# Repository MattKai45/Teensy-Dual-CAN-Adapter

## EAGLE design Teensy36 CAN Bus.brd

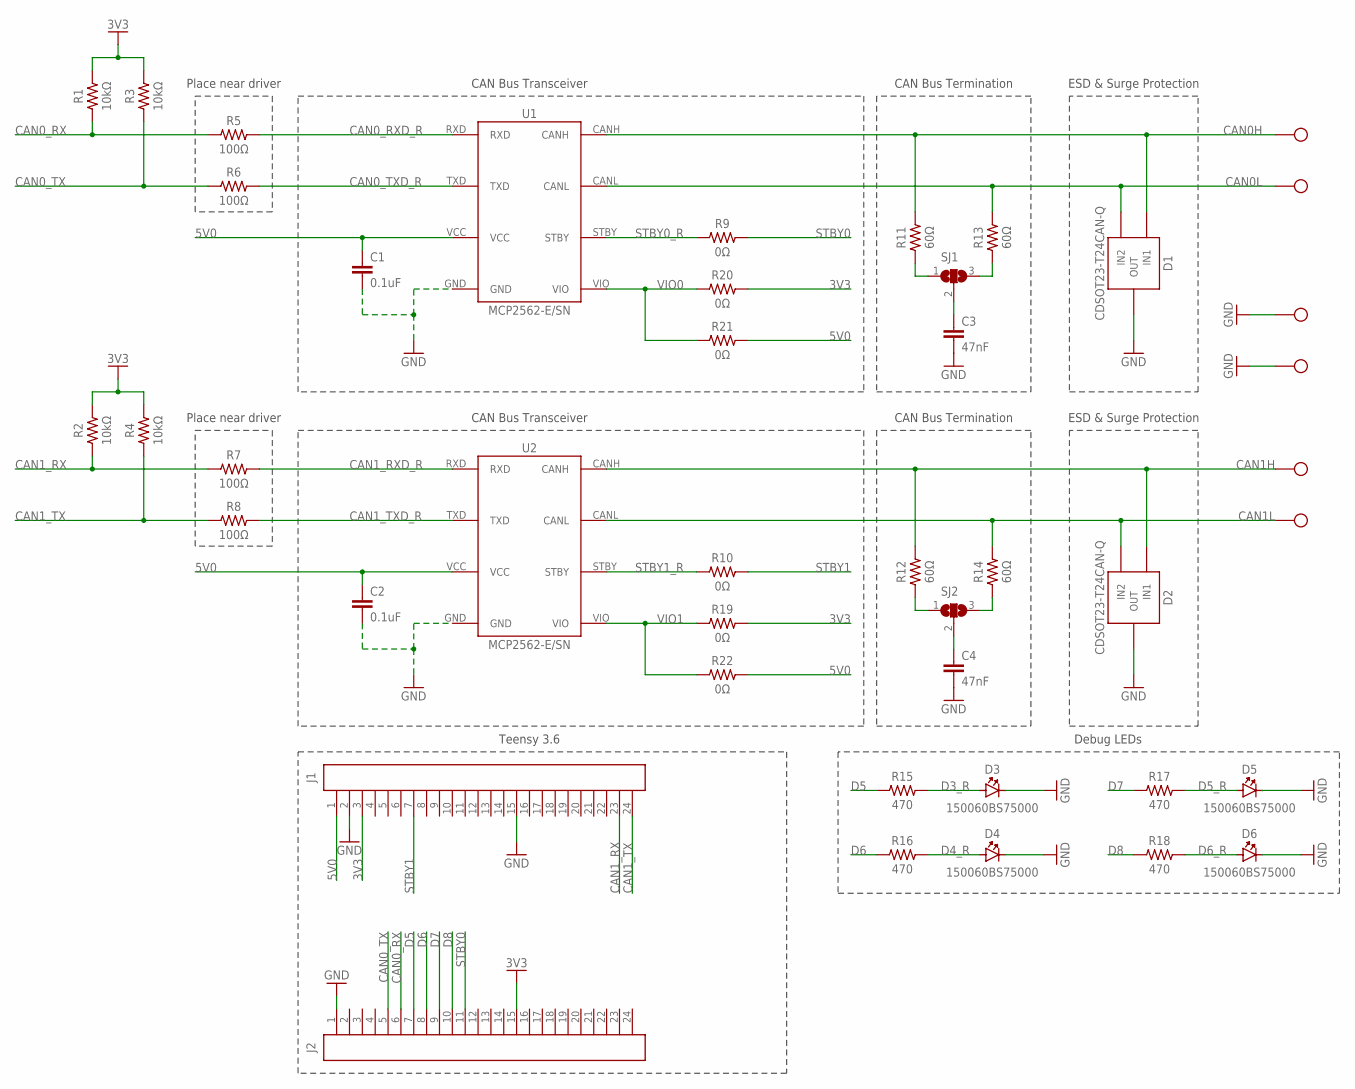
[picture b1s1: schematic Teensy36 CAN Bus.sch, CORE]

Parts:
C1, C2: 0.1uF; CAP-0603
C3, C4: 47nF; CAP-0603
D1, D2: CDSOT23-T24CAN-Q; BOURNS_CDSOT23-T24CAN-Q
D3, D4, D5, D6: LED_BLUE_0603_WURTH; WURTH_0603_LED
J1, J2: CONN_24PIN_VERT; CONN_100MIL_24_PIN
J3, J4, J5, J6, J7, J8: SOLDER_POINT; SMD_PAD_100X200
R1, R2, R3, R4: 10kΩ; REST-0603
R5, R6, R7, R8: 100Ω; REST-0603
R9, R10, R19, R20, R21, R22: 0Ω; REST-0603
R11, R12, R13, R14: 60Ω; REST-0603
R15, R16, R17, R18: 470; REST-0603
SJ1, SJ2: SJ2W; SJ_2
U1, U2: SN65HVD230DR; MICROCHIP_MCP2562

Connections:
3V3: J1.3, J2.15, R1.2, R2.2, R3.2, R4.2, R19.2, R20.2
5V0: C1.1, C2.1, J1.1, R21.2, R22.2, U1.VCC, U2.VCC
CAN0H: D1.IN2 (IN1), J5.P$1, R11.2, U1.CANH
CAN0L: D1.IN1 (IN2), J6.P$1, R13.2, U1.CANL
CAN0_CM: R13.1, SJ1.3
CAN0_RX: J2.6, R1.1, R5.1
CAN0_RXD_R: R5.2, U1.RXD
CAN0_TX: J2.5, R3.1, R6.1
CAN0_TXD_R: R6.2, U1.TXD
CAN1H: D2.IN2 (IN1), J3.P$1, R12.2, U2.CANH
CAN1L: D2.IN1 (IN2), J4.P$1, R14.2, U2.CANL
CAN1_RX: J1.23, R2.1, R7.1
CAN1_RXD_R: R7.2, U2.RXD
CAN1_TX: J1.24, R4.1, R8.1
CAN1_TXD_R: R8.2, U2.TXD
D3_R: D3.A, R15.2
D4_R: D4.A, R16.2
D5: J2.7, R15.1
D5_R: D5.A, R17.2
D6: J2.8, R16.1
D6_R: D6.A, R18.2
D7: J2.9, R17.1
D8: J2.10, R18.1
GND: C1.2, C2.2, C3.2, C4.2, D1.COMMON (OUT), D2.COMMON (OUT), D3.C, D4.C, D5.C, D6.C, J1.2, J1.15, J2.1, J7.P$1, J8.P$1, U1.GND, U2.GND
unnamed: R11.1, SJ1.1
unnamed: C3.1, SJ1.2
unnamed: R12.1, SJ2.1
unnamed: R14.1, SJ2.3
unnamed: C4.1, SJ2.2
STBY0: J2.11, R9.2
STBY0_R: R9.1, U1.STBY
STBY1: J1.7, R10.2
STBY1_R: R10.1, U2.STBY
VIO0: R20.1, R21.1, U1.VIO
VIO1: R19.1, R22.1, U2.VIO

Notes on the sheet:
ESD & Surge Protection
CAN Bus Termination
CAN Bus Transceiver
Place near driver
Teensy 3.6
Debug LEDs

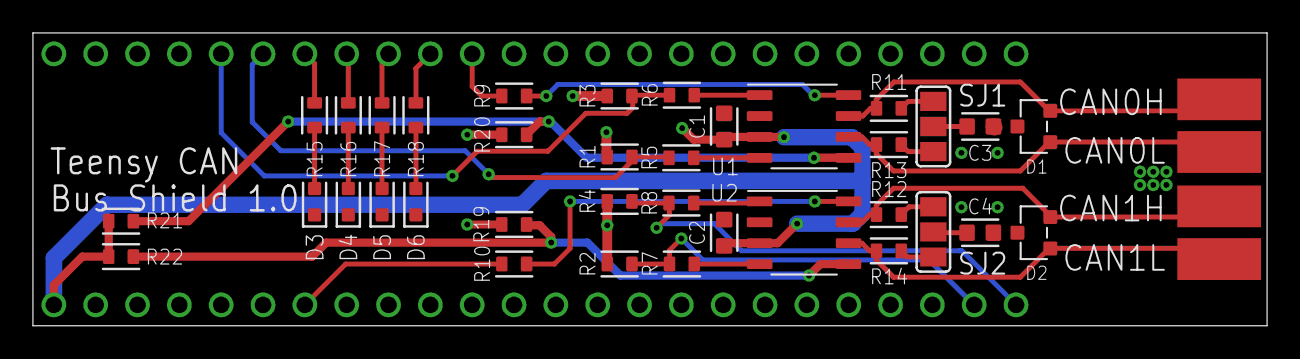
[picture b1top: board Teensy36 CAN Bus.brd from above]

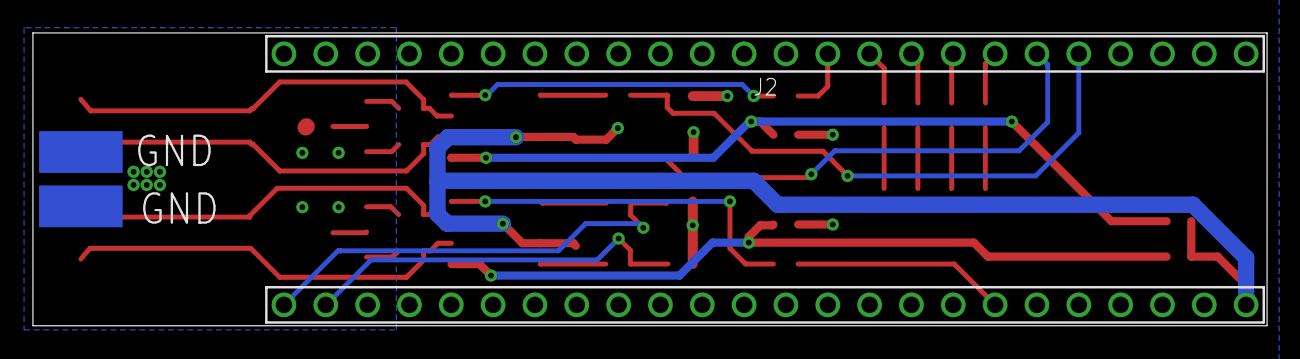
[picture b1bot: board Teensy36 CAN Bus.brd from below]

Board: 2 copper layers, 74.9 x 17.8 mm, 44 parts (4 on the bottom side), 35 nets.

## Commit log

2020-04-05 Design files initial commit
2020-07-10 Update Teensy pinout
